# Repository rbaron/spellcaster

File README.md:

spellcaster is a home automation magic wand. Click on the thumbnail above to watch it in action.

# How does it work?
An accelerometer and gyroscope are used to capture gestures ("spells"). Cast spells are then compared against previously stored ones. An action is triggered if there's a good match.

Different actions can be triggered. For example:
- A [BTHome.io](https://bthome.io) Bluetooth Low Energy (BLE) packet can be emitted and handled in [Home Assistant](https://www.home-assistant.io/).
- A Zigbee Cluster action, similarly handled in Home Assistant automations
- A [BLE-HID](https://novelbits.io/bluetooth-hid-devices-an-intro/) to simulate a key press on a computer, macro pad-style

In the "Software" section below, there are some firmware samples for each of these actions and more.

[This blog post](https://rbaron.net/blog/2023/10/27/spellcaster-a-home-automation-magic-wand.html) has a deeper dive into how everything works.

# Project status
It sort of works, but there are caveats. Reliability and usability need improvement -- it's easy to [hold it wrong](https://www.wired.com/2010/06/iphone-4-holding-it-wrong/). See "User interface" below. The code also needs the proverbial cleaning up.

Approach this project as a fun experiment. Expect fun and experimental support.

# Hardware

* [nRF52833](https://www.nordicsemi.com/Products/nRF52833) MCU
* [LSM6DSL](https://www.st.com/en/mems-and-sensors/lsm6dsl.html) IMU
* [Mini vibration motor](https://www.aliexpress.com/item/1005004653448729.html) for tactile feedback
* Powered by 2xAAA batteries

The [`kicad/`](./kicad/) directory contains the design and fabrication files. I used [JLCPCB](https://jlcpcb.com/) for manufacturing and assembly.

# User interface
## Casting spells
There is no on/off switch by design. To signal the *start of spell*, hold the wand horizontally flat. Once you start moving it, the gesture will start to be collected. To signal the *end of spell*, hold the wand horizontally flat again. Spells need to be between 500 milliseconds and 3 seconds in length.

## Record mode
To store a new spell in slot `S`, press the `A` button `S` times and cast a spell as described above. If everything goes well, the LED will flash five times and you will be switched to replay mode.

In this video you can see five different spells being recorded:

## Replay mode
This is the default mode in which spellcaster will live most of its life. Once a spell is cast, it will be compared to previously stored spells. If a good match is found, a vibration pattern is executed and an action will be triggered.

### On false positives
The matching algorithm is optimized for _something to happen_. There is a low threshold for matching spells, and often two or more will be sufficiently matched. This depends on how similar spells are, but the best matching spell will always be selected. The idea is that, when we intentionally cast a spell, the correct one will almost always be selected, instead of -- sometimes -- none. On the other hand, previously unseen spells may trigger a false positive.

This is done to mainly prevent the sorry sight of a full grown adult waving a wand in the air in front of friends and family at a dinner party and nothing happening. Don't ask. A better solution is to further tune the spell matching algorithm to be more robust against these cases, while retaining the precision when the casting is intentional. Another idea is to add an invisible capacitive touch sensor to the handle, which would also allow for much deeper sleep modes. Something to be improved.

## Deep sleep mode
If spellcaster is still for 10 seconds, it will enter the lowest power mode at around 65 uA. Most of which goes to the accelerometer, which lies semi-awake in a low power state waiting for movement. This can mostly likely be optimized further. Any movement will wake it up and into replay mode.

# Software
There are a few sample firmwares in the repository. They are all written with Nordic's [nRF Connect SDK](https://www.nordicsemi.com/Products/Development-software/nRF-Connect-SDK). Most samples are adapted from the SDK's examples.

| Directory | Description |
| --- | --- |
|[`code/sclib`](./code/sclib/)| Generic spellcaster library. Handles spell casting, storing and signal processing. Used by all other samples.|
|[`code/samples/ble-bthome`](./code/samples/ble-bthome/)|Matched spell `S` trigger a [BTHome.io](https://bthome.io) action that is equivalent to `S` button presses. This can then be used by [Home Assistant](https://homeassistant.io) automations. |
|[`code/samples/ble-hid`](./code/samples/ble-hid/)|spellcaster pairs with your computer via BLE. Matched spell `S` trigger a BLE-HID action that simulates a key press following the configurable [keymap](https://github.com/rbaron/spellcaster/blob/fc7ee0511366e4b62a08713fc59aa67fac9f286a/code/samples/ble-hid/src/main.c#L16).|
|[`code/samples/zigbee`](./code/samples/zigbee/)|Matched spells trigger Zigbee Cluster actions that can be used by [Home Assistant](https://homeassistant.io) automations. Unfortunately, the Zigbee specs don't define magic wand clusters, so the [spellcaster.py ZHA Quirk](https://github.com/rbaron/spellcaster/blob/main/code/samples/zigbee/zha/quirks/spellcaster.py) needs to be installed. With it, matched spell on slot `S` appears to be a "dim light" command with step `S`. Yikes! (And it's not even the worst hack around here). |
|[`code/samples/ble-dump`](./code/samples/ble-dump/)|Dumps raw accel & gyro spells over BLE. The [client.py](https://github.com/rbaron/spellcaster/blob/main/code/samples/ble-dump/client/client.py) connects to spellcaster and dumps the data to a file. This is how I collected the data for tuning the spell matching without cables getting in the way.|

## Building the samples
These are standard nRF Connect SDK projects with Zephyr RTOS, and the [official docs](https://nrfconnect.github.io/vscode-nrf-connect/index.html) apply. The [b-parasite project](https://github.com/rbaron/b-parasite) uses a similar setup with a generic library and different samples, and [the Wiki](https://github.com/rbaron/b-parasite/wiki/How-to-Build-the-Firmware-Samples) contains more details and alternatives.

## Flashing the samples
The samples are flashed with ARM's usual [SWD](https://developer.arm.com/documentation/ihi0031/a/The-Serial-Wire-Debug-Port--SW-DP-/Introduction-to-the-ARM-Serial-Wire-Debug--SWD--protocol). The [official docs](https://nrfconnect.github.io/vscode-nrf-connect/get_started/quick_debug.html) also apply. The only caveat is the custom, slim 6-testpoint SWD pins on the PCB. It also happens to the the exact same as described in the [b-parasite Wiki](https://github.com/rbaron/b-parasite/wiki/How-to-Flash-the-Firmware-Samples).

# Data analysis
The [`data/`](./data/) directory contains a bunch of Jupyter notebooks I used to tune the spell matching and some of the raw collected data.

# 3D printed case

The [`3dprint/`](./3dprint/) directory contains the STEP files for a 3D printed case. It's okay-ish, but could use some love. The 3D printed springs lose some tension after a while, and so do the clamps that hold both halves together. On the bright side, there's no glue nor screws involved. You can watch a video of the full assembly process [here](https://www.youtube.com/watch?v=kVlnX7w-8rc).

# License
## Hardware
spellcaster hardware © 2023 by rbaron is licensed under Creative Commons Attribution-ShareAlike 4.0 International (CC BY-SA 4.0). See [deed](https://creativecommons.org/licenses/by-sa/4.0/).

## Software
Software in this repository is licensed under the [MIT license](https://opensource.org/licenses/MIT). See [LICENSE_SOFTWARE](./LICENSE_SOFTWARE).

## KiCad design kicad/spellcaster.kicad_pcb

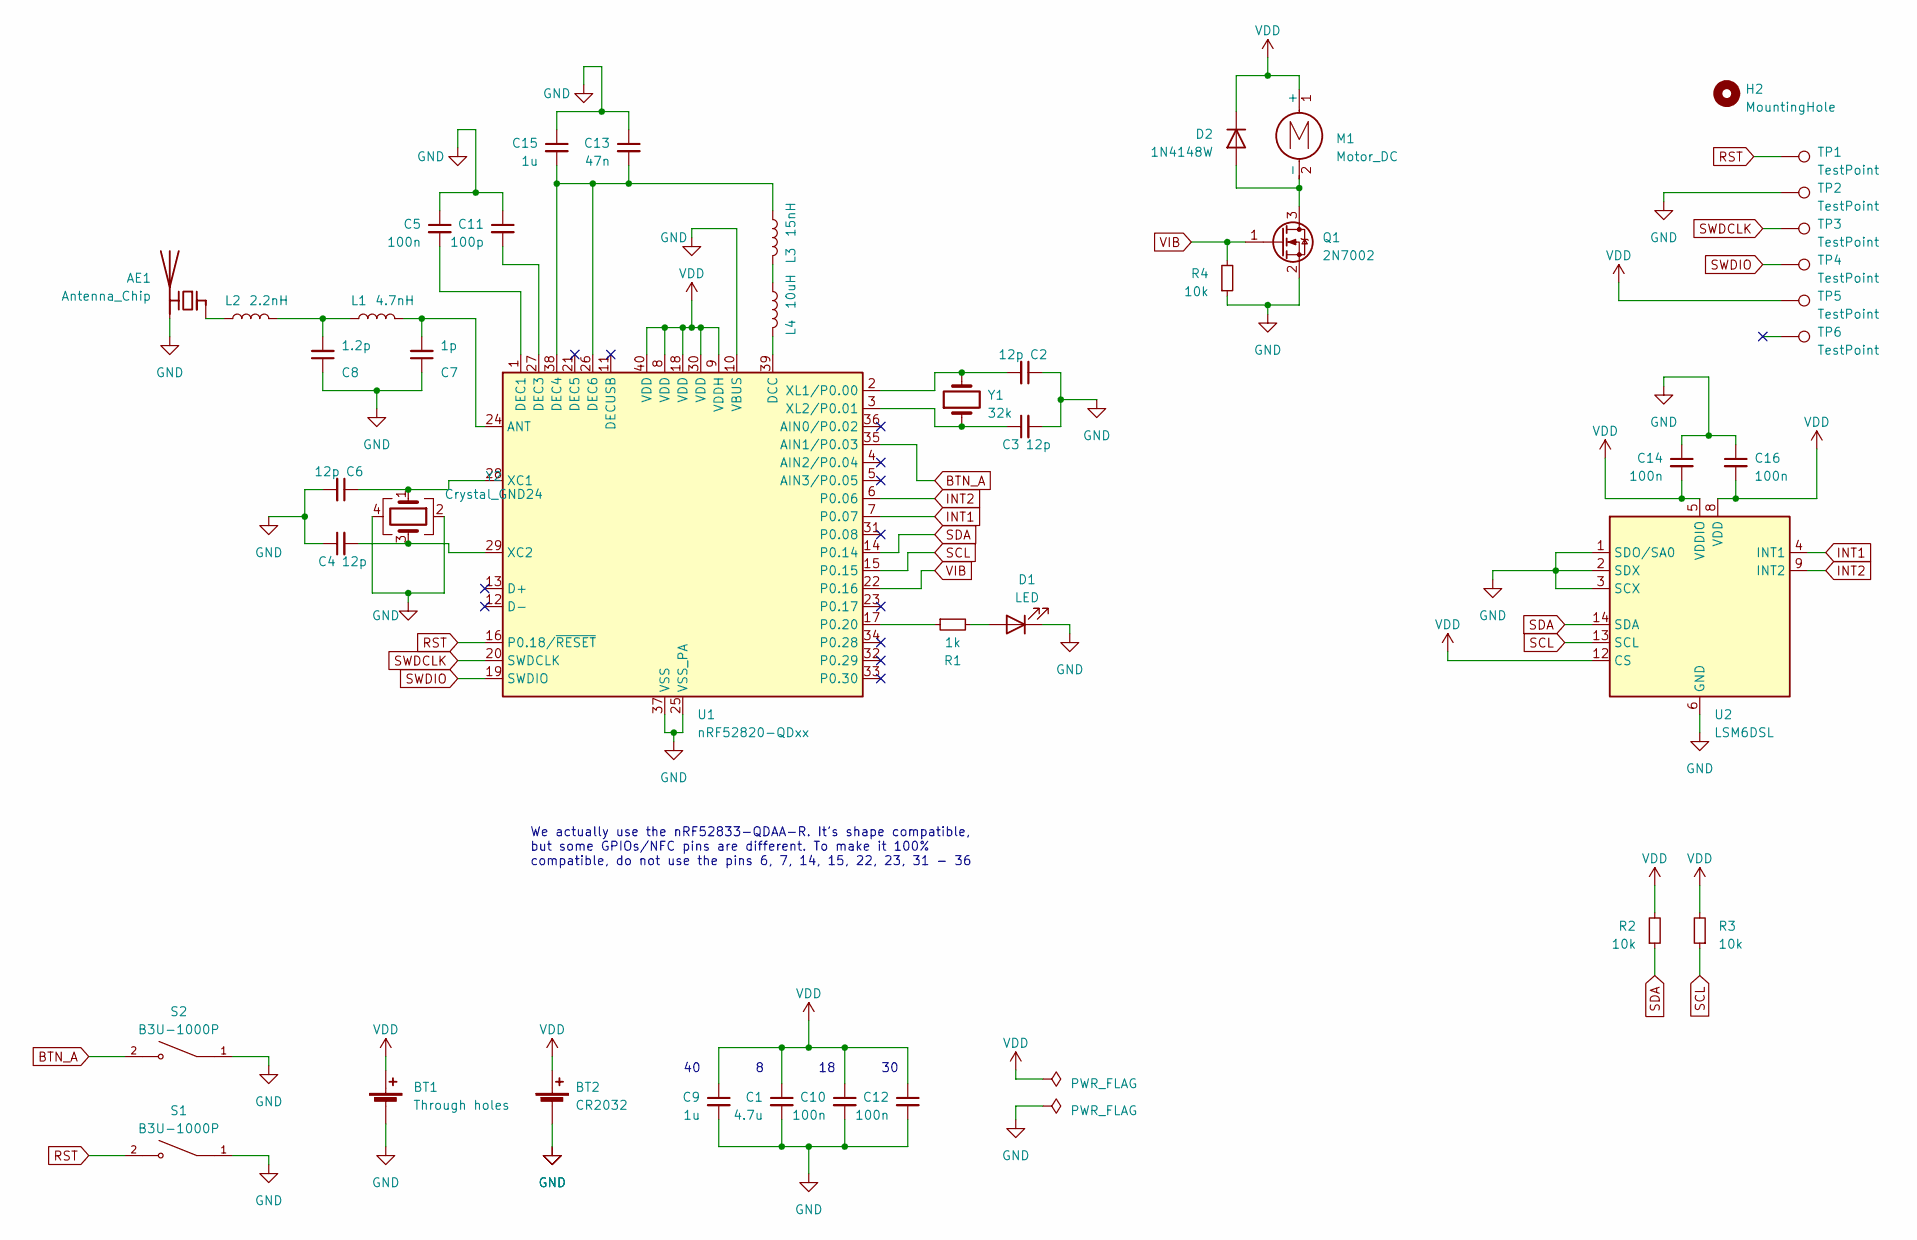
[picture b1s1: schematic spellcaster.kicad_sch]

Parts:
AE1: Antenna_Chip; Texas_SWRA117D_2.4GHz_Right
BT1: Through holes; SolderWire-0.5sqmm_1x02_P4.8mm_D0.9mm_OD2.3mm
BT2: CR2032; BatteryHolder_Keystone_1060_1x2032
C1: 4.7u; C_0402_1005Metric; LCSC C368809
C2, C3, C4, C6: 12p; C_0402_1005Metric; LCSC C1547
C5, C10, C12, C14, C16: 100n; C_0402_1005Metric; LCSC C1525
C7: 1p; C_0402_1005Metric; LCSC C1550
C8: 1.2p; C_0402_1005Metric; LCSC C1551
C9, C15: 1u; C_0402_1005Metric; LCSC C52923
C11: 100p; C_0402_1005Metric; LCSC C1546
C13: 47n; C_0402_1005Metric; LCSC C237221
D1: LED; LED_0603_1608Metric; LCSC C2286
D2: 1N4148W; D_SOD-323; LCSC C2128
H2: MountingHole; MountingHole_2.2mm_M2_Pad_Via
L1: 4.7nH; L_0402_1005Metric; LCSC C963987
L2: 2.2nH; L_0402_1005Metric; LCSC C108254
L3: 15nH; L_0402_1005Metric; LCSC C27143
L4: 10uH; L_1206_3216Metric; LCSC C1051
M1: Motor_DC; TestPoint_2Pads_Pitch2.54mm_Drill0.8mm
Q1: 2N7002; SOT-23; LCSC C8545
R1: 1k; R_0402_1005Metric; LCSC C11702
R2, R3, R4: 10k; R_0402_1005Metric; LCSC C60490
S1, S2: B3U-1000P; SW_B3U-1000P; LCSC C231329
TP1, TP2, TP3, TP4, TP5, TP6: TestPoint; TestPoint_Pad_D1.5mm
U1: nRF52820-QDxx; QFN-40-1EP_5x5mm_P0.4mm_EP3.6x3.6mm; LCSC C2895249
U2: LSM6DSL; LGA-14_3x2.5mm_P0.5mm_LayoutBorder3x4y; LCSC C126672
Y1: 32k; Crystal_SMD_3215-2Pin_3.2x1.5mm; LCSC C32346
Y2: Crystal_GND24; Crystal_SMD_2016-4Pin_2.0x1.6mm; LCSC C2149195

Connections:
BTN_A: S2.2, U1.35 (AIN1/P0.03)
GND: AE1.2 (PCB_Trace), BT1.2 (-), BT2.2 (-), C1.2, C2.1, C3.2, C4.1, C5.1, C6.2, C7.1, C8.1, C9.2, C10.2, C11.1, C12.2, C13.1, C14.1, C15.1, C16.1, D1.1 (K), Q1.2 (S), R4.1, S1.1, S2.1, TP2.1, U1.10 (VBUS), U1.25 (VSS_PA), U1.37 (VSS), U1.41 (VSS), U2.1 (SDO/SA0), U2.2 (SDX), U2.3 (SCX), U2.6 (GND), U2.7 (GND), Y2.2, Y2.4
INT1: U1.7 (P0.07), U2.4 (INT1)
INT2: U1.6 (P0.06), U2.9 (INT2)
unnamed: AE1.1 (FEED), L2.1
unnamed: C8.2, L1.1, L2.2
unnamed: D1.2 (A), R1.2
unnamed: D2.2 (A), M1.2 (-), Q1.3 (D)
unnamed: L3.1, L4.2
unnamed: C7.2, L1.2, U1.24 (ANT)
unnamed: L4.1, U1.39 (DCC)
unnamed: C5.2, U1.1 (DEC1)
unnamed: C11.2, U1.27 (DEC3)
unnamed: C13.2, C15.2, L3.2, U1.26 (DEC6), U1.38 (DEC4)
unnamed: R1.1, U1.17 (P0.20)
unnamed: C6.1, U1.28 (XC1), Y2.1
unnamed: C4.2, U1.29 (XC2), Y2.3
unnamed: C2.2, U1.2 (XL1/P0.00), Y1.2
unnamed: C3.1, U1.3 (XL2/P0.01), Y1.1
RST: S1.2, TP1.1, U1.16 (P0.18/~RESET)
SCL: R3.1, U1.15 (P0.15), U2.13 (SCL)
SDA: R2.1, U1.14 (P0.14), U2.14 (SDA)
SWDCLK: TP3.1, U1.20 (SWDCLK)
SWDIO: TP4.1, U1.19 (SWDIO)
VDD: BT1.1 (+), BT2.1 (+), C1.1, C9.1, C10.1, C12.1, C14.2, C16.2, D2.1 (K), M1.1 (+), R2.2, R3.2, TP5.1, U1.8 (VDD), U1.9 (VDDH), U1.18 (VDD), U1.30 (VDD), U1.40 (VDD), U2.5 (VDDIO), U2.8 (VDD), U2.12 (CS)
VIB: Q1.1 (G), R4.2, U1.22 (P0.16)

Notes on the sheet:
We actually use the nRF52833-QDAA-R. It's shape compatible, but some GPIOs/NFC pins are different. To make it 100% compatible, do not use the pins 6, 7, 14, 15, 22, 23, 31 - 36

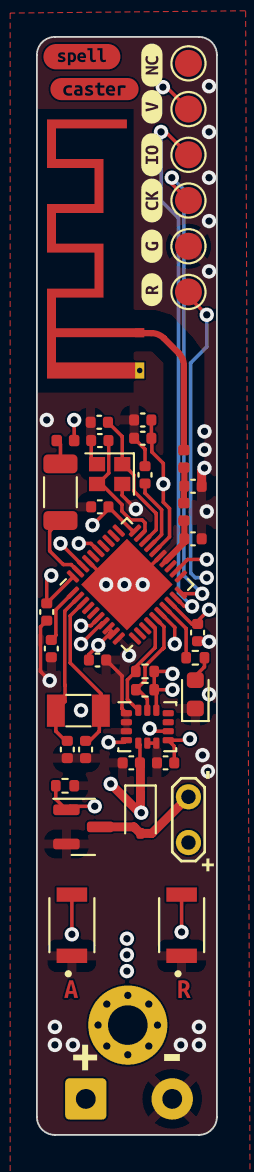
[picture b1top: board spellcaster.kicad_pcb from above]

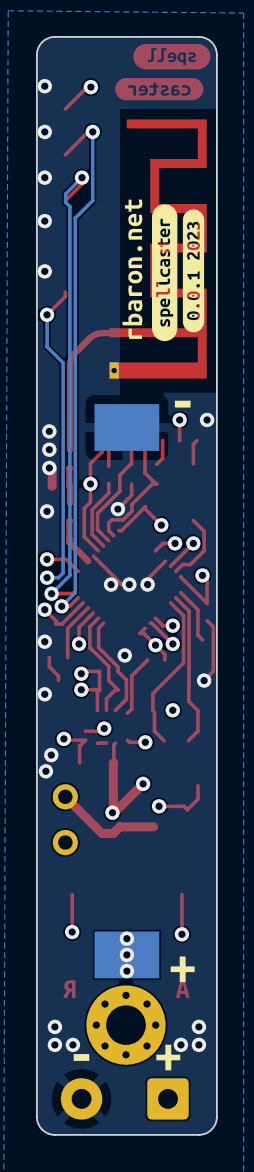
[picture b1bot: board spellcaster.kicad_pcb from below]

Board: 4 copper layers, 10.0 x 61.0 mm, 65 parts (8 on the bottom side), 26 nets.

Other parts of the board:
kibuzzard-64E66B38: G***; kibuzzard-64E66B38
kibuzzard-64E70B5B: G***; kibuzzard-64E70B5B
kibuzzard-64E70C98: G***; kibuzzard-64E70C98
kibuzzard-64E666A5: G***; kibuzzard-64E666A5
kibuzzard-64E666BF: G***; kibuzzard-64E666BF
kibuzzard-64E666C8: G***; kibuzzard-64E666C8
kibuzzard-64E666DB: G***; kibuzzard-64E666DB
kibuzzard-64E666EE: G***; kibuzzard-64E666EE
kibuzzard-64E668FF, kibuzzard-64E668FF#2, kibuzzard-64E668FF#3: G***; kibuzzard-64E668FF
kibuzzard-64E704EF: G***; kibuzzard-64E704EF
kibuzzard-64E705F6: G***; kibuzzard-64E705F6
kibuzzard-64E7057C: G***; kibuzzard-64E7057C
kibuzzard-64E7063C: G***; kibuzzard-64E7063C
kibuzzard-64E66706: G***; kibuzzard-64E66706
kibuzzard-64E66855: G***; kibuzzard-64E66855
kibuzzard-64E66915, kibuzzard-64E66915#2: G***; kibuzzard-64E66915
kibuzzard-64E70501: G***; kibuzzard-64E70501
kibuzzard-64E70567: G***; kibuzzard-64E70567

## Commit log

2023-08-13 Initial commit
    Sample `check` seems to compile
2023-08-14 Ported some Arduino prototype code
2023-08-14 caster-test records & calls back
2023-08-15 Ported obw/ble-bthome
    Still needs lots of memory opt. Currently CONFIG_ASSERT makes it almost
    run out of RAM
2023-08-15 ble-bthome + caster kinda works for two slots
    But RAM is close to full, had to limit signal storage to 2s
2023-08-16 Found RAM hogger! DTW[INF]
2023-08-16 Storing signals to flash seems to work
2023-08-21 Copied and renamed obw's kicad proj here
2023-08-23 Initial routing
2023-08-23 Smaller, graphics
2023-08-23 Round edges
2023-08-23 Silkscreen + stitching
2023-08-24 Add vibration motor
2023-08-24 Fixes vibration motor routing
2023-08-24 Add optional CR2032 holder
2023-08-24 Fixed missing accel vcc connection
2023-08-24 DRC happy
2023-08-24 Plotted and ordered
2023-08-25 Fixed wrong package for D1
2023-08-30 Updated D1 footprint
    ... After feedback from JLC engineers. This is the actual produced
    version 0.0.1
2023-09-01 0.0.1 kinda works
    Accel readings mostly work, ay is odd
2023-09-01 ported input-ble-bthome
    Works at avg 4.67 uA!
2023-09-15 [accel] Reading gyro & accel works -- hacky
2023-09-16 [caster] Uncomment logic
2023-09-16 Quick hack for dumping signals to RTT
2023-09-17 kinda works
2023-09-17 New data
2023-09-17 Added pcb STEP
2023-10-06 I honestly don't remember, but things seem to work
2023-10-07 V0 case (white PETG)
2023-10-08 Updated case
    Not ideal, but works with some massaging
2023-10-08 PWM for vibration & some improvements to state machine
2023-10-09 [ble-dump] Initial service & client works, now needs real data
2023-10-09 [ble-dump] Kinda works
2023-10-09 Simpe ble-dump dumps & jupyter notebook
2023-10-10 [ble-bthome] Kinda works ok now!
2023-10-10 More flash space (no MCUBoot), DFW uses window
    Seems to work well, but I disabled sleeping. It was buggy.
    Next:
    - Fix sleeping
    - Fix horizontal position somehow
2023-10-11 I think sleeping works?
2023-10-13 Rotation invariance works... In theory (notebook)
2023-10-14 Rotation invariance works!
2023-10-17 Vib async, lower horiz timer to 250 ms (max samples = 2.4s still)
2023-10-24 Some Jupyter plots
2023-10-25 Port one-bit-wonder's zigbee sample
2023-10-25 ble-hid works, but I'm gonna have to undo a lot of hacks
    Main issue took a while to figure out: CONFIG_SETTINGS (&
    CONFIG_BT_SETTINGS) also use the `storage` partition. Since we use it at
    the same time for LittleFS, shit goes down and it's really hard to
    debug. Just a bunch of gibberish in logs, which I thought it was a stack
    overflow and chased that wrong thread for hours...
2023-10-25 ble-hid sliiiightly less hacky, but still pretty bad
2023-10-26 Optimize DTW windowing RAM usage
    Seems to work, but needs more testing.
2023-10-26 Removed zigbee memory hack
2023-10-29 6 button press, max signals lengths diff
2023-10-29 Add uptick dump
2023-11-05 Minor tweaks
2024-03-29 Fixed (?) state machine
2024-05-06 Real README.md
2024-11-01 Add latest 3dprint files
2024-11-01 License files
2024-11-01 Format LICENSE_SOFTWARE
